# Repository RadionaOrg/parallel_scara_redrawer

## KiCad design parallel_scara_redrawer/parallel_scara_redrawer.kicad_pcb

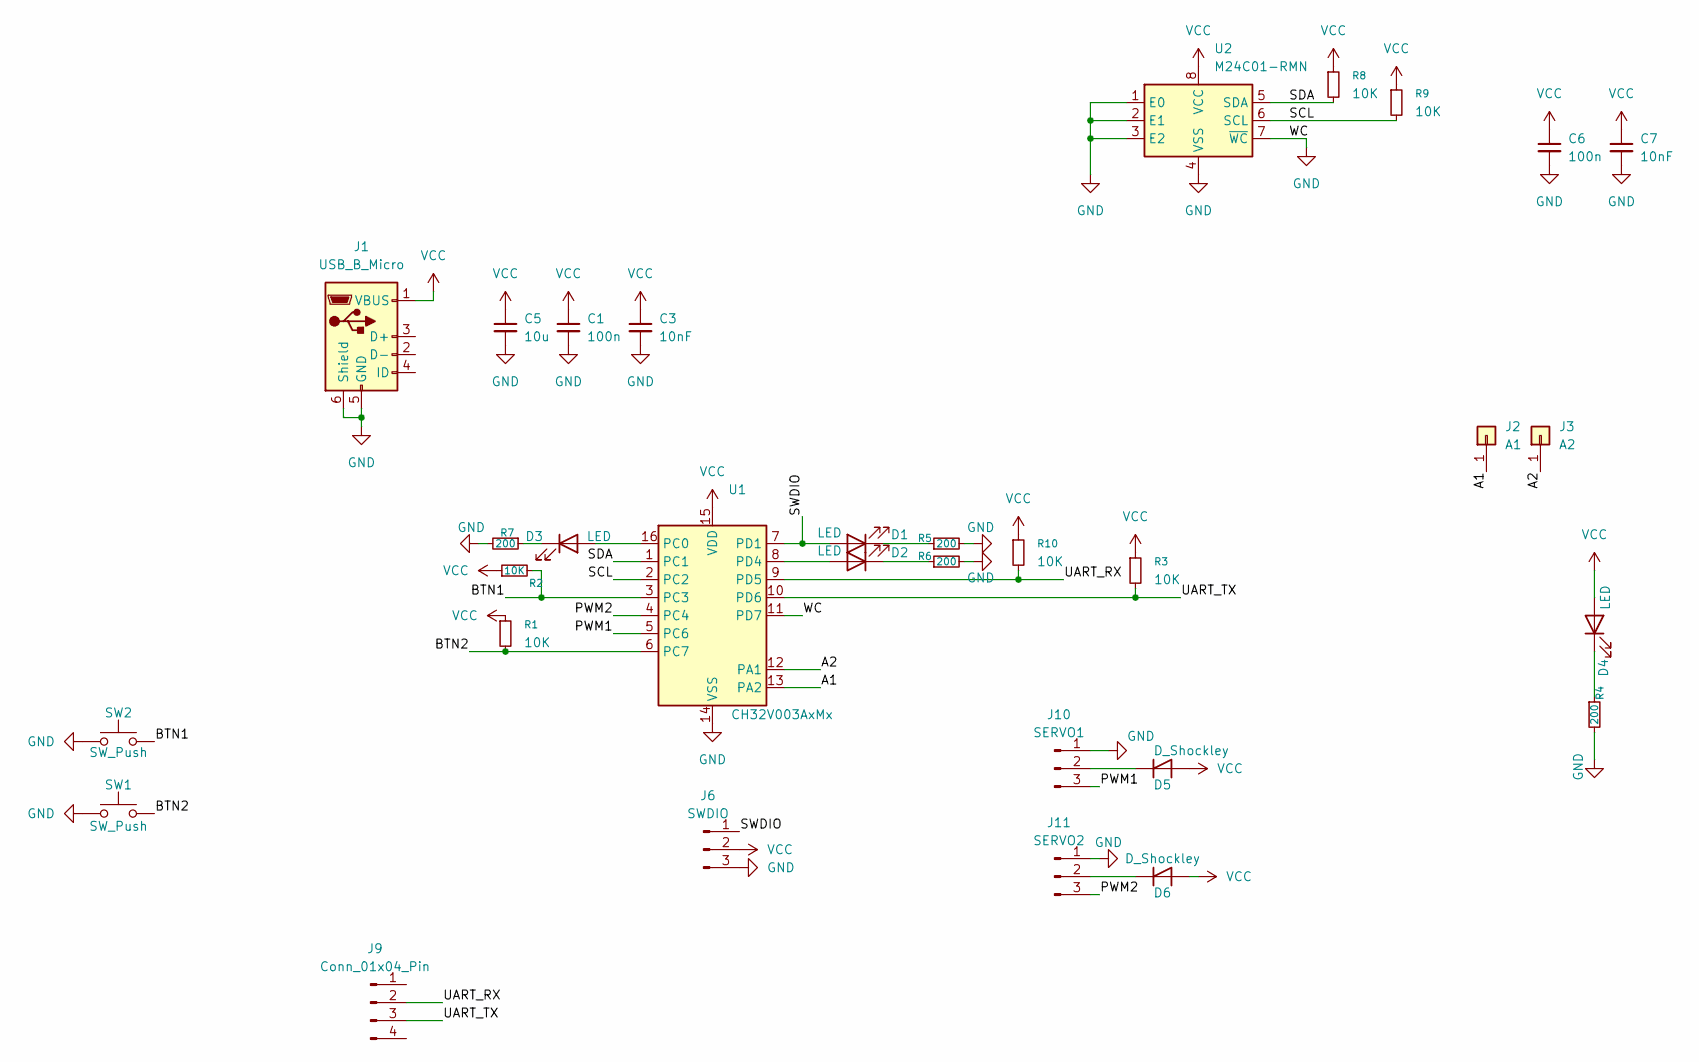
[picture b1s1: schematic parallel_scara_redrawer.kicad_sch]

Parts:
C1, C6: 100n; C_0603_1608Metric_Pad1.08x0.95mm_HandSolder
C3, C7: 10nF; C_0603_1608Metric_Pad1.08x0.95mm_HandSolder
C5: 10u; C_0603_1608Metric_Pad1.08x0.95mm_HandSolder
D1, D2, D3, D4: LED; LED_0603_1608Metric_Pad1.05x0.95mm_HandSolder
D5, D6: D_Shockley; D_SMA
J1: USB_B_Micro; USB_Micro-B_Wuerth_629105150521
J2: A1; PinSocket_1x01_P2.54mm_Vertical
J3: A2; PinSocket_1x01_P2.54mm_Vertical
J6: SWDIO; PinSocket_1x03_P2.54mm_Vertical
J9: Conn_01x04_Pin; PinSocket_1x04_P2.54mm_Vertical
J10: SERVO1; PinSocket_1x03_P2.54mm_Vertical
J11: SERVO2; PinSocket_1x03_P2.54mm_Vertical
R1, R2, R3, R8, R9, R10: 10K; R_0603_1608Metric_Pad0.98x0.95mm_HandSolder
R4, R5, R6, R7: 200; R_0603_1608Metric_Pad0.98x0.95mm_HandSolder
SW1, SW2: SW_Push; SW_SPST_EVPBF
U1: CH32V003AxMx; SOP-16_3.9x9.9mm_P1.27mm
U2: M24C01-RMN; SOIC-8_3.9x4.9mm_P1.27mm

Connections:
/A1: J2.1, U1.13 (PA2)
/A2: J3.1, U1.12 (PA1)
/BTN1: R2.2, SW2.2, U1.3 (PC3)
/BTN2: R1.2, SW1.2, U1.6 (PC7)
/PWM1: J10.3, U1.5 (PC6)
/PWM2: J11.3, U1.4 (PC4)
/SCL: R9.2, U1.2 (PC2), U2.6 (SCL)
/SDA: R8.2, U1.1 (PC1), U2.5 (SDA)
/SWDIO: D1.2 (A), J6.1, U1.7 (PD1)
/UART_RX: J9.2, R10.2, U1.9 (PD5)
/UART_TX: J9.3, R3.2, U1.10 (PD6)
GND: C1.2, C3.2, C5.2, C6.2, C7.2, J1.5 (GND), J1.6 (Shield), J6.3, J10.1, J11.1, R4.2, R5.2, R6.2, R7.2, SW1.1, SW2.1, U1.11 (PD7), U1.14 (VSS), U2.1 (E0), U2.2 (E1), U2.3 (E2), U2.4 (VSS), U2.7 (~WC)
unnamed: D1.1 (K), R5.1
unnamed: D2.2 (A), U1.8 (PD4)
unnamed: D2.1 (K), R6.1
unnamed: D3.2 (A), U1.16 (PC0)
unnamed: D3.1 (K), R7.1
unnamed: D4.1 (K), R4.1
unnamed: D5.1 (K), J10.2
unnamed: D6.1 (K), J11.2
VCC: C1.1, C3.1, C5.1, C6.1, C7.1, D4.2 (A), D5.2 (A), D6.2 (A), J1.1 (VBUS), J6.2, R1.1, R2.1, R3.1, R8.1, R9.1, R10.1, U1.15 (VDD), U2.8 (VCC)

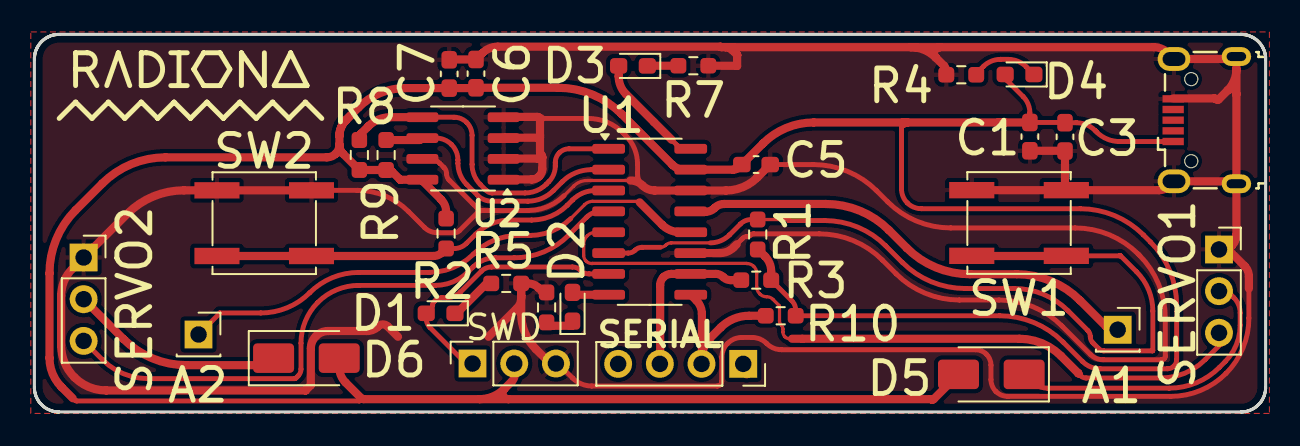
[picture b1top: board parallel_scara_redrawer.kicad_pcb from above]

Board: 2 copper layers, 75.0 x 23.0 mm, 33 parts (0 on the bottom side), 21 nets.

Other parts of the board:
radiona: radiona

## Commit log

2025-07-26 Adding initial version
